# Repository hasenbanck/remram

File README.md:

# RemRam - 3D printer controller

## Features

 * 32bit STM32F765VI
   * 216 MHz
   * 512 KBytes RAM
   * 2 MBytes flash
 * 4x TMC2130 stepper driver
   * stealthChop
   * spreadCycle
   * coolStep
   * stallGuard
 * 24V main power rail
   * heatbed output (15A)
   * heater output (5A)
   * stepper driver and logic (5A)
 * 5V secondary power rail (3A)
   * FAN1 and FAN2
 * 2x 3.3V tertiary power rail (2x 0.5A)
   * MCU power (IO)
   * SD card power
 * Robust connectors
 * Quality, high powered MOSFET
 * 4 layer board with single side component placement

## PCB design

Software used KiCad 5.0

### Alternative Parts

You can substitute the TPS5408 with a TPS5402. In this case you also need to replace R4 with a Zero Ohm resistor.

## Compiling the firmware

 1. [Install Arduino](https://www.arduino.cc/en/Main/Software)
 2. [Install the STM32 Core](https://github.com/stm32duino/wiki/wiki/Getting-Started)
 3. Optional for Serial over USB support: [Update the STM32 Core using the git repository](https://github.com/stm32duino/wiki/wiki/Using-git-repository)
 4. [Download the current git branch of Marlin 2.0](https://github.com/MarlinFirmware/Marlin/tree/bugfix-2.0.x)
 5. Open the Marlin project, select the "RemRam V1" board from the Marlin menue, edit the Marlin configuration file and build the project. You need to find the HEX or BIN file that Arduino creates and flash the firmware onto the board (See: "How to flash the firmware").

## Configure Marlin

These are the board specific ```Configuration.h``` changes:
```C
#define SERIAL_PORT 1 // 1 = UART connection on EXT3
                      // -1 = Serial over USB (see: Virtual COM Port Support (Serial over USB))
                      // You can also configure SERIAL_PORT_2

#define BAUDRATE 115200 // 115200 for UART on EXT3
                        // 1000000 for Serial over USB

#define MOTHERBOARD BOARD_REMRAM_V1

#define X_DRIVER_TYPE  TMC2130
#define Y_DRIVER_TYPE  TMC2130
#define Z_DRIVER_TYPE  TMC2130
#define E0_DRIVER_TYPE TMC2130

#define ENDSTOP_INTERRUPTS_FEATURE

#define SDSUPPORT
```

These are the board specific ```Configuration_adv.h``` changes:
```C
#define MINIMUM_STEPPER_DIR_DELAY 20
#define MINIMUM_STEPPER_PULSE 0
#define MAXIMUM_STEPPER_RATE 400000

#if HAS_TRINAMIC

  // You can change ever value EXCEPT R_SENSE based on your setup.
  // Example values of my HEVO setup

  #define R_SENSE           0.12  // DO NOT CHANGE! Need to be 0.12 for RemRam V1
  #define HOLD_MULTIPLIER    0.3  // Scales down the holding current from run current
  #define INTERPOLATE       true  // Interpolate X/Y/Z_MICROSTEPS to 256

  #define X_CURRENT          750  // rms current in mA. Multiply by 1.41 for peak current.
  #define X_MICROSTEPS       256  // 0..256

  #define Y_CURRENT          750
  #define Y_MICROSTEPS       256

  #define Z_CURRENT          750
  #define Z_MICROSTEPS       256

  #define E0_CURRENT         400
  #define E0_MICROSTEPS      256

  #define STEALTHCHOP
  #define MONITOR_DRIVER_STATUS

  #if ENABLED(MONITOR_DRIVER_STATUS)
    #define CURRENT_STEP_DOWN     50  // [mA]
    #define REPORT_CURRENT_CHANGE
    #define STOP_ON_ERROR
  #endif

  #define SENSORLESS_HOMING // If you want to use sensorless homing

  #if ENABLED(SENSORLESS_HOMING) || ENABLED(SENSORLESS_PROBING)
    #define X_STALL_SENSITIVITY  2
    #define Y_STALL_SENSITIVITY  2
    #define Z_STALL_SENSITIVITY  2
  #endif

  #define TMC_DEBUG // Helpfull when setting up your system

#endif
```

```src/pins/pins_REMRAM_V1.h```
```C
// Use only one or the other (you could damage the hardware otherwise!)
#define SDSS               57   // Onboard SD card reader
//#define SDSS              9   // LCD SD card reader
```

Of course you need to aditionally change the configuration files based on your particular printer setup.

## Virtual COM Port Support (Serial over USB)

Virtual COM Port (also known as VCOM or CDC) support will land in the "official" STM32 arduino core with version 1.5.0. If you want to use VCOM feature earlier, you can use the the [master branch of the offical core](https://github.com/stm32duino/Arduino_Core_STM32).

Have a look at the "[Update the STM32 Core using the git repository](https://github.com/stm32duino/wiki/wiki/Using-git-repository)" on how to update the STM32 arduino core with a custom git branch. You also have to select "CDC Full Speed" as USB interface inside Arduino to enable the CDC interface.

## External SD card reader

Most RepRapDiscount based LCD modules come with an integrated SD card reader. You can use this reader, but because this system is 3.3V based, the signal to noise ration is higher. Meaning you will need a much better connection between the LCD module and the board. Crappy ribbon cables won't do it in most cases. Dropping the SPI speed AND using shielded ribbon cables is most likely needed to get a good signal integrity.

You can't use the onboard SD card reader and the LCD card reader at the same time. DO NOT insert a SD card in both slots at the same time, because this could lead to a hardware failure.

## How to flash the firmware

Supported:

 * Using the Cortex Debug Header (SWD)
 * Using DFU over USB
 * Using UART on EXT-3 PIN 15 (TX) and PIN 16 (RX)

### Cortex Debug Header

You can use the Cortex Debug Header to program the STM32 firmware and do step-by-step debugging.

This board only support SWD. SWO is not routed to the header, since we had to use the
pin for a PWM output.

I personally use the SEGGER J-Link Edu Mini. But any 2€ Ebay flasher should work ("ST Link V2").
Please make sure that you have a adapter for the debug header!

The debug header is a 2x05 pin (1.27/0.05”).

### DFU (USB)

https://www.st.com/en/development-tools/stsw-stm32080.html

Please pay attention that you don't just flash the HEX/BIN file, but the special DFU image file (*.dfu) you need to create with the "DFU file manager" tool. DfuSe will let you happily flash a HEX/BIN file, but the board won't boot without a propper DFU file.

Please read the "UM0412" user manual you can find at the above link.

### UART

https://www.st.com/en/development-tools/flasher-stm32.html

## LICENSE

CERN OHL version 1.2

The files under PCB/packages3d are excluded from this license and are provided under fair use terms for this open-source project.

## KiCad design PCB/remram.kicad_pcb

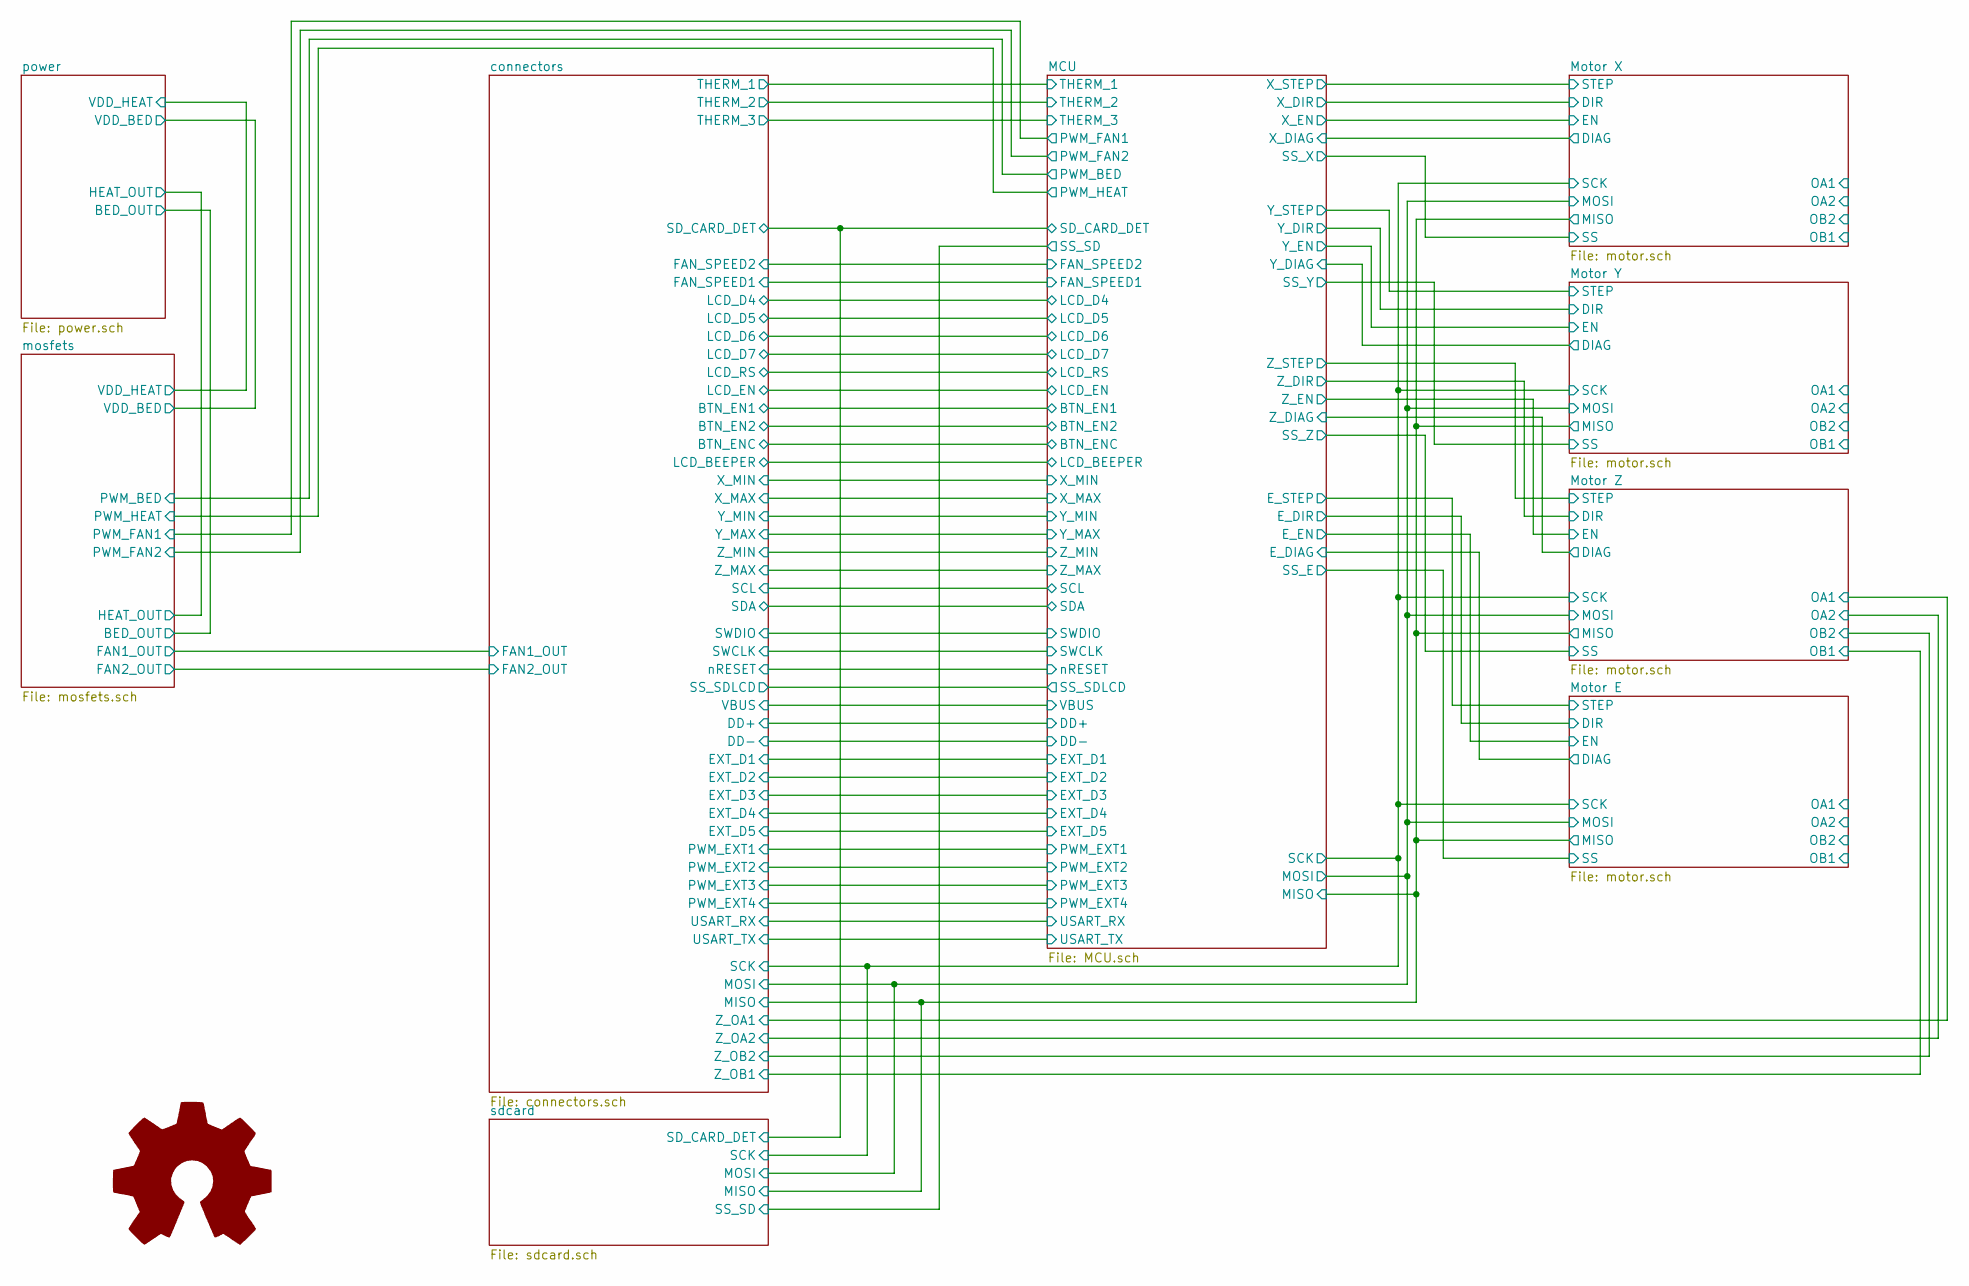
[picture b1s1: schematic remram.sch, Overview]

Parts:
LOGO1: Logo_Open_Hardware_Large; OSHW-Logo2_14.6x12mm_SilkScreen

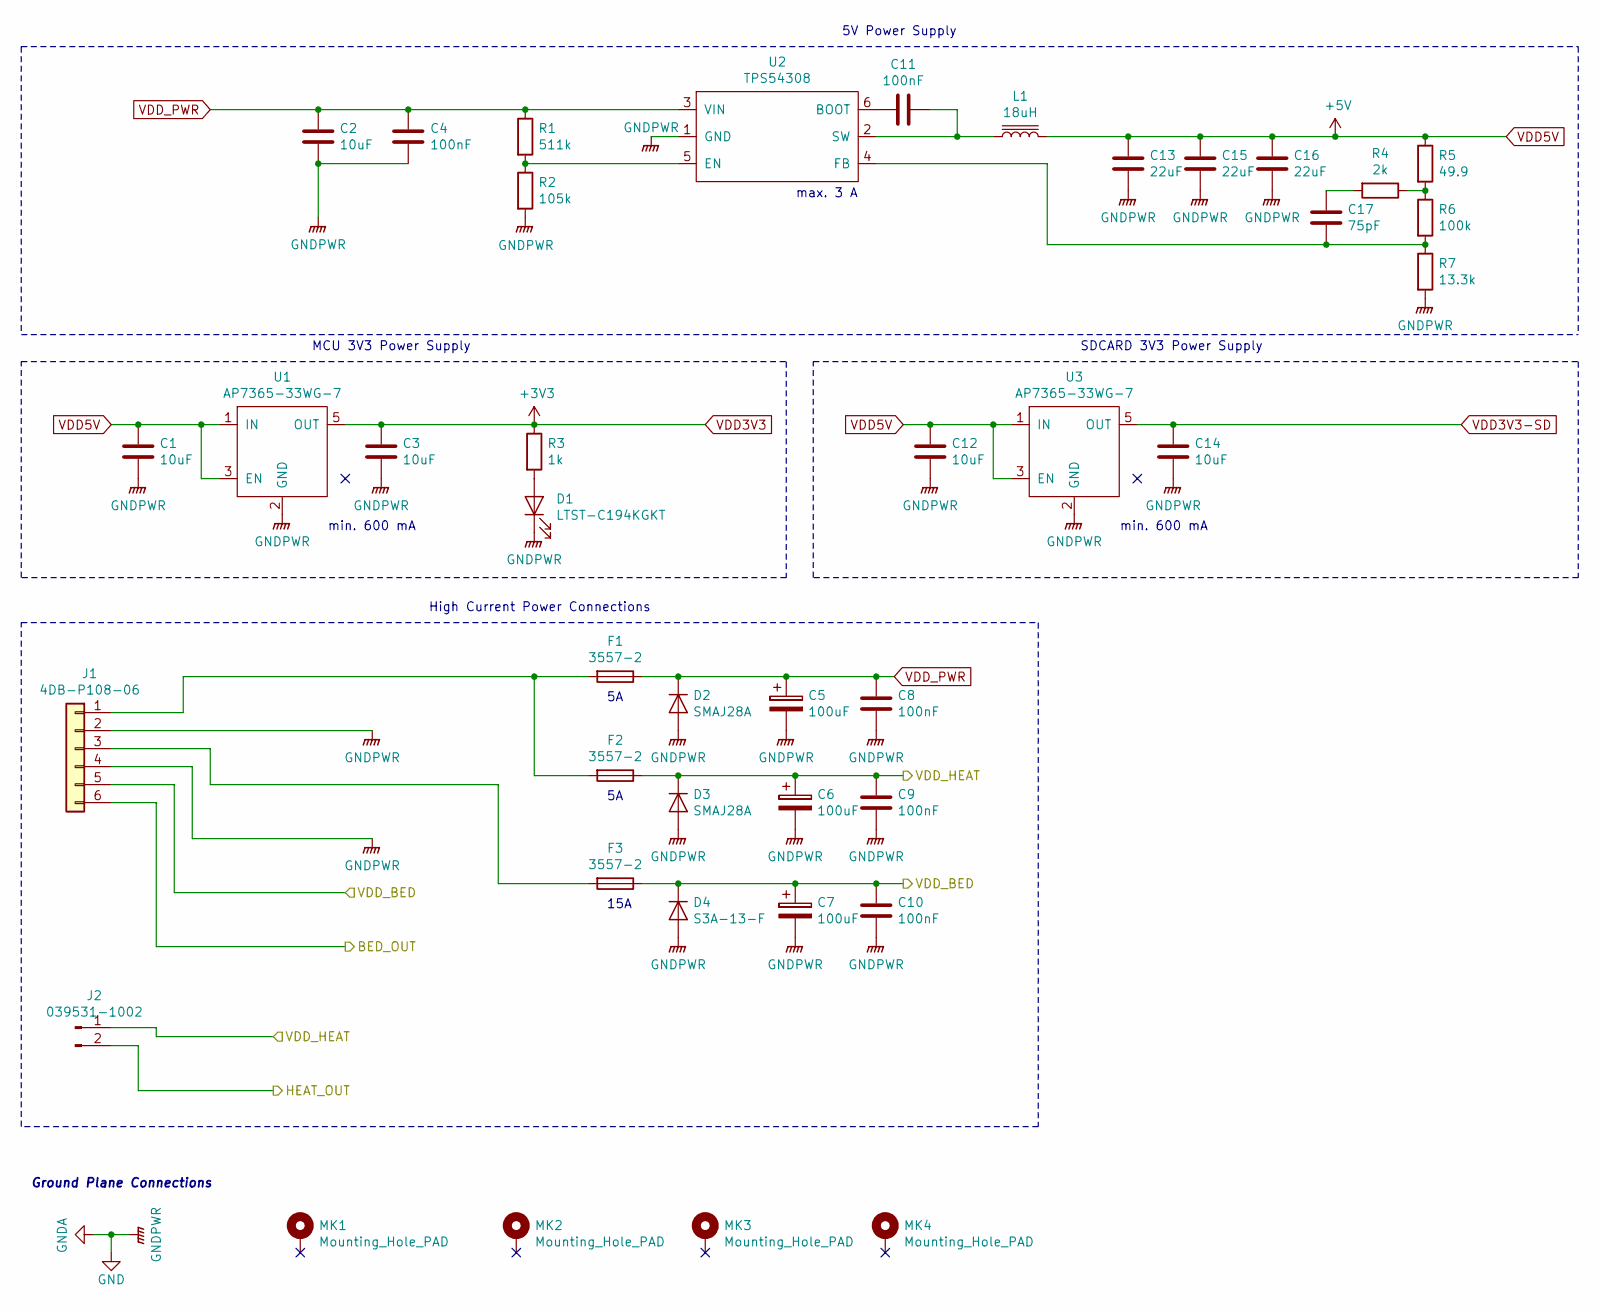
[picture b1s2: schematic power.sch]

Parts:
C1, C3, C12, C14: 10uF; C_0603_1608Metric
C2: 10uF; C_1206_3216Metric
C4: 100nF; C_1206_3216Metric
C5, C6, C7: 100uF; CP_Radial_D6.3mm_P2.50mm
C8, C9, C10: 100nF; C_1812_4532Metric
C11: 100nF; C_0603_1608Metric
C13, C15, C16: 22uF; C_1206_3216Metric
C17: 75pF; C_0603_1608Metric
D1: LTST-C194KGKT; LED_0603_1608Metric
D2, D3: SMAJ28A; D_SMA
D4: S3A-13-F; D_SMC
F1, F2, F3: 3557-2; KEYSTONE-FUSE-3557-2
J1: 4DB-P108-06
J2: 039531-1002; 39531-1002
L1: 18uH; L_Wuerth_WE-PDF
MK1, MK2, MK3, MK4: Mounting_Hole_PAD; MountingHole_3.5mm_Pad
R1: 511k; R_0603_1608Metric
R2: 105k; R_0603_1608Metric
R3: 1k; R_0603_1608Metric
R4: 2k; R_0603_1608Metric
R5: 49.9; R_0603_1608Metric
R6: 100k; R_0603_1608Metric
R7: 13.3k; R_0603_1608Metric
U1, U3: AP7365-33WG-7; SOT-23-5
U2: TPS54308; SOT-23-6

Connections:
/mosfets/BED_OUT: J1.6; also elsewhere on the board
/mosfets/HEAT_OUT: J2.2; also elsewhere on the board
/mosfets/VDD_BED: C7.1, C10.1, D4.1 (K), F3.1, J1.5; also elsewhere on the board
/mosfets/VDD_HEAT: C6.1, C9.1, D3.1 (K), F2.1, J2.1; also elsewhere on the board
GND: C1.2, C2.2, C3.2, C4.2, C5.2, C6.2, C7.2, C8.2, C9.2, C10.2, C12.2, C13.2, C14.2, C15.2, C16.2, D1.1 (K), D2.2 (A), D3.2 (A), D4.2 (A), J1.2, J1.4, R2.2, R7.2, U1.2 (GND), U2.1 (GND), U3.2 (GND); also elsewhere on the board
unnamed: C11.1, U2.6 (BOOT)
unnamed: C11.2, L1.1, U2.2 (SW)
unnamed: C17.1, R4.2
unnamed: C17.2, R6.2, R7.1, U2.4 (FB)
unnamed: D1.2 (A), R3.2
unnamed: F1.2, F2.2, J1.1
unnamed: F3.2, J1.3
unnamed: R1.2, R2.1, U2.5 (EN)
unnamed: R4.1, R5.2, R6.1
VDD3V3: C3.1, R3.1, U1.5 (OUT); also elsewhere on the board
VDD3V3-SD: C14.1, U3.5 (OUT); also elsewhere on the board
VDD5V: C1.1, C12.1, C13.1, C15.1, C16.1, L1.2, R5.1, U1.1 (IN), U1.3 (EN), U3.1 (IN), U3.3 (EN); also elsewhere on the board
VDD_PWR: C2.1, C4.1, C5.1, C8.1, D2.1 (K), F1.1, R1.1, U2.3 (VIN); also elsewhere on the board

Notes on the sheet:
min. 600 mA
max. 3 A
15A
Ground Plane Connections
High Current Power Connections
5V Power Supply
MCU 3V3 Power Supply
SDCARD 3V3 Power Supply

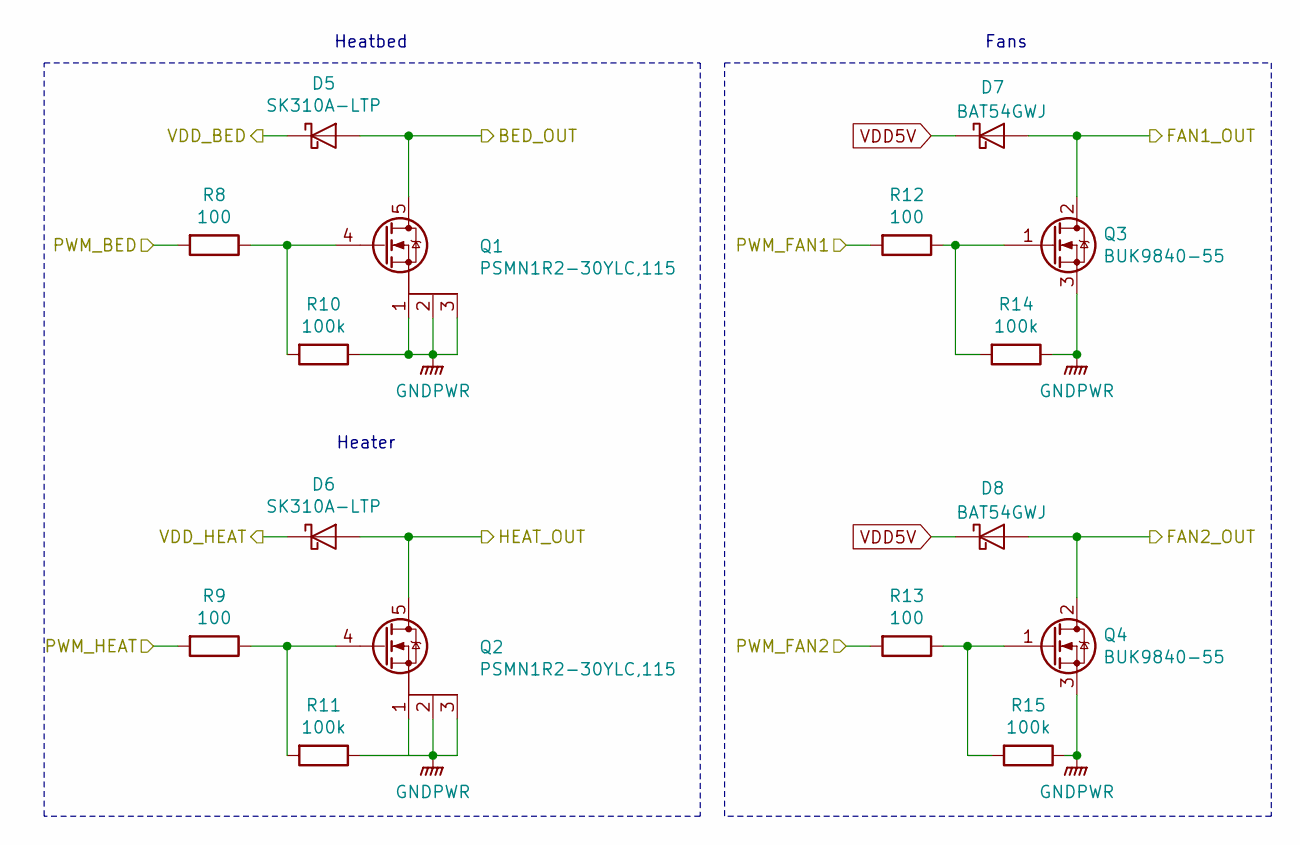
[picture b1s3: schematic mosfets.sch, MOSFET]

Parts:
D5, D6: SK310A-LTP; D_SMA
D7, D8: BAT54GWJ; D_SOD-123
Q1, Q2: PSMN1R2-30YLC,115; SOT-669_LFPAK_ThermalVias-1
Q3, Q4: BUK9840-55; SOT-223-3_TabPin2
R8, R9, R12, R13: 100; R_0603_1608Metric
R10, R11, R14, R15: 100k; R_0603_1608Metric

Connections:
/MCU/PWM_BED: R8.2; also elsewhere on the board
/MCU/PWM_FAN1: R12.2; also elsewhere on the board
/MCU/PWM_FAN2: R13.2; also elsewhere on the board
/MCU/PWM_HEAT: R9.2; also elsewhere on the board
/connectors/FAN1_OUT: D7.2 (A), Q3.2 (D); also elsewhere on the board
/connectors/FAN2_OUT: D8.2 (A), Q4.2 (D); also elsewhere on the board
/mosfets/BED_OUT: D5.2 (A), Q1.5 (D); also elsewhere on the board
/mosfets/HEAT_OUT: D6.2 (A), Q2.5 (D); also elsewhere on the board
/mosfets/VDD_BED: D5.1 (K); also elsewhere on the board
/mosfets/VDD_HEAT: D6.1 (K); also elsewhere on the board
GND: Q1.1 (S), Q1.2 (S), Q1.3 (S), Q2.1 (S), Q2.2 (S), Q2.3 (S), Q3.3 (S), Q4.3 (S), R10.1, R11.1, R14.1, R15.1; also elsewhere on the board
unnamed: Q1.4 (G), R8.1, R10.2
unnamed: Q2.4 (G), R9.1, R11.2
unnamed: Q3.1 (G), R12.1, R14.2
unnamed: Q4.1 (G), R13.1, R15.2
VDD5V: D7.1 (K), D8.1 (K); also elsewhere on the board

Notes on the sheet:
Heater
Heatbed
Fans

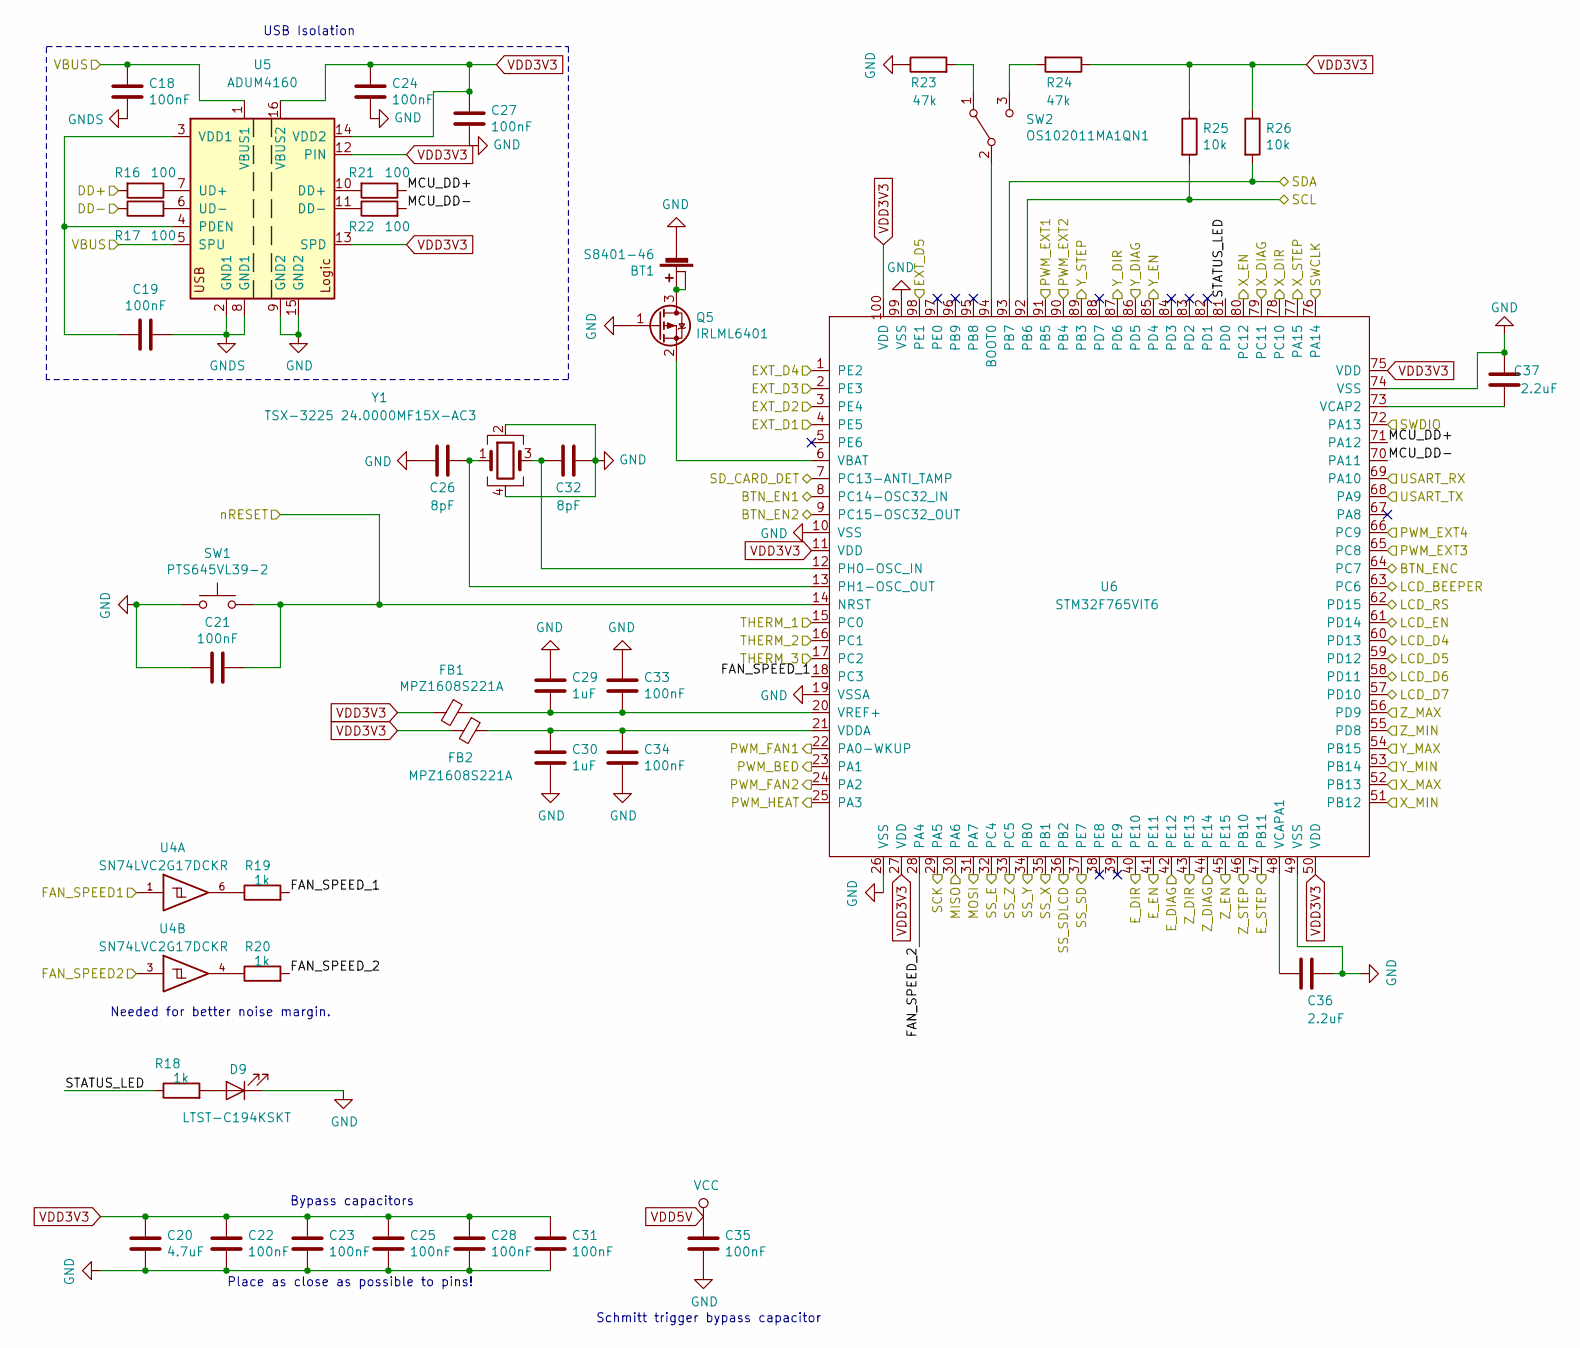
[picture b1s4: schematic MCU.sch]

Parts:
BT1: S8401-46
C18, C19, C21, C22, C23, C24, C25, C27, C28, C31, C33, C34, C35: 100nF; C_0603_1608Metric
C20: 4.7uF; C_0603_1608Metric
C26, C32: 8pF; C_0603_1608Metric
C29, C30: 1uF; C_0603_1608Metric
C36, C37: 2.2uF; C_0603_1608Metric
D9: LTST-C194KSKT; LED_0603_1608Metric
FB1, FB2: MPZ1608S221A; R_0603_1608Metric
Q5: IRLML6401; SOT-23
R16, R17, R21, R22: 100; R_0603_1608Metric
R18, R19, R20: 1k; R_0603_1608Metric
R23, R24: 47k; R_0603_1608Metric
R25, R26: 10k; R_0603_1608Metric
SW1: PTS645VL39-2; SW_Tactile_SPST_Angled_PTS645Vx39-2LFS
SW2: OS102011MA1QN1; SW_CuK_OS102011MA1QN1_SPDT_Angled
U4: SN74LVC2G17DCKR; SOT-363_SC-70-6
U5: ADUM4160; SOIC-16W_7.5x10.3mm_P1.27mm
U6: STM32F765VIT6; TQFP-100_14x14mm_P0.5mm
Y1: TSX-3225 24.0000MF15X-AC3; Crystal_SMD_SeikoEpson_TSX3225-4Pin_3.2x2.5mm

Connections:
/MCU/BTN_EN1: U6.8 (PC14-OSC32_IN); also elsewhere on the board
/MCU/BTN_EN2: U6.9 (PC15-OSC32_OUT); also elsewhere on the board
/MCU/BTN_ENC: U6.64 (PC7); also elsewhere on the board
/MCU/DD+: R16.2; also elsewhere on the board
/MCU/DD-: R17.1; also elsewhere on the board
/MCU/EXT_D1: U6.4 (PE5); also elsewhere on the board
/MCU/EXT_D2: U6.3 (PE4); also elsewhere on the board
/MCU/EXT_D3: U6.2 (PE3); also elsewhere on the board
/MCU/EXT_D4: U6.1 (PE2); also elsewhere on the board
/MCU/EXT_D5: U6.98 (PE1); also elsewhere on the board
/MCU/E_STEP: U6.47 (PB11); also elsewhere on the board
/MCU/FAN_SPEED1: U4.1; also elsewhere on the board
/MCU/FAN_SPEED2: U4.3; also elsewhere on the board
/MCU/FAN_SPEED_1: R19.2, U6.18 (PC3)
/MCU/FAN_SPEED_2: R20.2, U6.28 (PA4)
/MCU/LCD_BEEPER: U6.63 (PC6); also elsewhere on the board
/MCU/LCD_D4: U6.60 (PD13); also elsewhere on the board
/MCU/LCD_D5: U6.59 (PD12); also elsewhere on the board
/MCU/LCD_D6: U6.58 (PD11); also elsewhere on the board
/MCU/LCD_D7: U6.57 (PD10); also elsewhere on the board
/MCU/LCD_EN: U6.61 (PD14); also elsewhere on the board
/MCU/LCD_RS: U6.62 (PD15); also elsewhere on the board
/MCU/MCU_DD+: R21.1, U6.71 (PA12)
/MCU/MCU_DD-: R22.2, U6.70 (PA11)
/MCU/MISO: U6.30 (PA6); also elsewhere on the board
/MCU/MOSI: U6.31 (PA7); also elsewhere on the board
/MCU/PWM_BED: U6.23 (PA1); also elsewhere on the board
/MCU/PWM_EXT1: U6.91 (PB5); also elsewhere on the board
/MCU/PWM_EXT2: U6.90 (PB4); also elsewhere on the board
/MCU/PWM_EXT3: U6.65 (PC8); also elsewhere on the board
/MCU/PWM_EXT4: U6.66 (PC9); also elsewhere on the board
/MCU/PWM_FAN1: U6.22 (PA0-WKUP); also elsewhere on the board
/MCU/PWM_FAN2: U6.24 (PA2); also elsewhere on the board
/MCU/PWM_HEAT: U6.25 (PA3); also elsewhere on the board
/MCU/SCK: U6.29 (PA5); also elsewhere on the board
/MCU/SCL: R25.2, U6.92 (PB6); also elsewhere on the board
/MCU/SDA: R26.2, U6.93 (PB7); also elsewhere on the board
/MCU/SD_CARD_DET: U6.7 (PC13-ANTI_TAMP); also elsewhere on the board
/MCU/SS_SD: U6.37 (PE7); also elsewhere on the board
/MCU/SS_SDLCD: U6.36 (PB2); also elsewhere on the board
/MCU/STATUS_LED: R18.1, U6.81 (PD0)
/MCU/SWCLK: U6.76 (PA14); also elsewhere on the board
/MCU/SWDIO: U6.72 (PA13); also elsewhere on the board
/MCU/THERM_1: U6.15 (PC0); also elsewhere on the board
/MCU/THERM_2: U6.16 (PC1); also elsewhere on the board
/MCU/THERM_3: U6.17 (PC2); also elsewhere on the board
/MCU/USART_RX: U6.69 (PA10); also elsewhere on the board
/MCU/USART_TX: U6.68 (PA9); also elsewhere on the board
/MCU/VBUS: C18.1, U5.1 (VBUS1), U5.5 (SPU); also elsewhere on the board
/MCU/X_MAX: U6.52 (PB13); also elsewhere on the board
/MCU/X_MIN: U6.51 (PB12); also elsewhere on the board
/MCU/Y_MAX: U6.54 (PB15); also elsewhere on the board
/MCU/Y_MIN: U6.53 (PB14); also elsewhere on the board
/MCU/Z_MAX: U6.56 (PD9); also elsewhere on the board
/MCU/Z_MIN: U6.55 (PD8); also elsewhere on the board
/MCU/nRESET: C21.2, SW1.2, U6.14 (NRST); also elsewhere on the board
/Motor E/DIAG: U6.42 (PE12); also elsewhere on the board
/Motor E/DIR: U6.40 (PE10); also elsewhere on the board
/Motor E/EN: U6.41 (PE11); also elsewhere on the board
/Motor E/SS: U6.32 (PC4); also elsewhere on the board
/Motor X/DIAG: U6.79 (PC11); also elsewhere on the board
/Motor X/DIR: U6.78 (PC10); also elsewhere on the board
/Motor X/EN: U6.80 (PC12); also elsewhere on the board
/Motor X/SS: U6.35 (PB1); also elsewhere on the board
/Motor X/STEP: U6.77 (PA15); also elsewhere on the board
/Motor Y/DIAG: U6.86 (PD5); also elsewhere on the board
/Motor Y/DIR: U6.87 (PD6); also elsewhere on the board
/Motor Y/EN: U6.85 (PD4); also elsewhere on the board
/Motor Y/SS: U6.34 (PB0); also elsewhere on the board
/Motor Y/STEP: U6.89 (PB3); also elsewhere on the board
/Motor Z/DIAG: U6.44 (PE14); also elsewhere on the board
/Motor Z/DIR: U6.43 (PE13); also elsewhere on the board
/Motor Z/EN: U6.45 (PE15); also elsewhere on the board
/Motor Z/SS: U6.33 (PC5); also elsewhere on the board
/Motor Z/STEP: U6.46 (PB10); also elsewhere on the board
GND: BT1.1 (-), C20.2, C21.1, C22.2, C23.2, C24.2, C25.2, C26.1, C27.1, C28.2, C29.1, C30.2, C31.2, C32.2, C33.1, C34.2, C35.2, C36.1, C37.2, D9.1 (K), Q5.1 (G), R23.1, SW1.1, U4.2 (GND), U5.9 (GND2), U5.15 (GND2), U6.10 (VSS), U6.19 (VSSA), U6.26 (VSS), U6.49 (VSS), U6.74 (VSS), U6.99 (VSS), Y1.2, Y1.4; also elsewhere on the board
GNDS: C18.2, C19.1, U5.2 (GND1), U5.8 (GND1); also elsewhere on the board
unnamed: BT1.2 (+), BT1.3 (+), Q5.3 (D)
unnamed: C19.2, U5.3 (VDD1), U5.4 (PDEN)
unnamed: C26.2, U6.13 (PH1-OSC_OUT), Y1.1
unnamed: C29.2, C33.2, FB1.1, U6.20 (VREF+)
unnamed: C30.1, C34.1, FB2.1, U6.21 (VDDA)
unnamed: C32.1, U6.12 (PH0-OSC_IN), Y1.3
unnamed: C36.2, U6.48 (VCAPA1)
unnamed: C37.1, U6.73 (VCAP2)
unnamed: D9.2 (A), R18.2
unnamed: Q5.2 (S), U6.6 (VBAT)
unnamed: R16.1, U5.7 (UD+)
unnamed: R17.2, U5.6 (UD-)
unnamed: R19.1, U4.6
unnamed: R20.1, U4.4
unnamed: R21.2, U5.10 (DD+)
unnamed: R22.1, U5.11 (DD-)
unnamed: R23.2, SW2.1 (A)
unnamed: R24.2, SW2.3 (C)
unnamed: SW2.2 (B), U6.94 (BOOT0)
VDD3V3: C20.1, C22.1, C23.1, C24.1, C25.1, C27.2, C28.1, C31.1, FB1.2, FB2.2, R24.1, R25.1, R26.1, U5.12 (PIN), U5.13 (SPD), U5.14 (VDD2), U5.16 (VBUS2), U6.11 (VDD), U6.27 (VDD), U6.50 (VDD), U6.75 (VDD), U6.100 (VDD); also elsewhere on the board
VDD5V: C35.1, U4.5 (VCC); also elsewhere on the board

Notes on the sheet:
Place as close as possible to pins!
Bypass capacitors
USB Isolation
Needed for better noise margin.
Schmitt trigger bypass capacitor

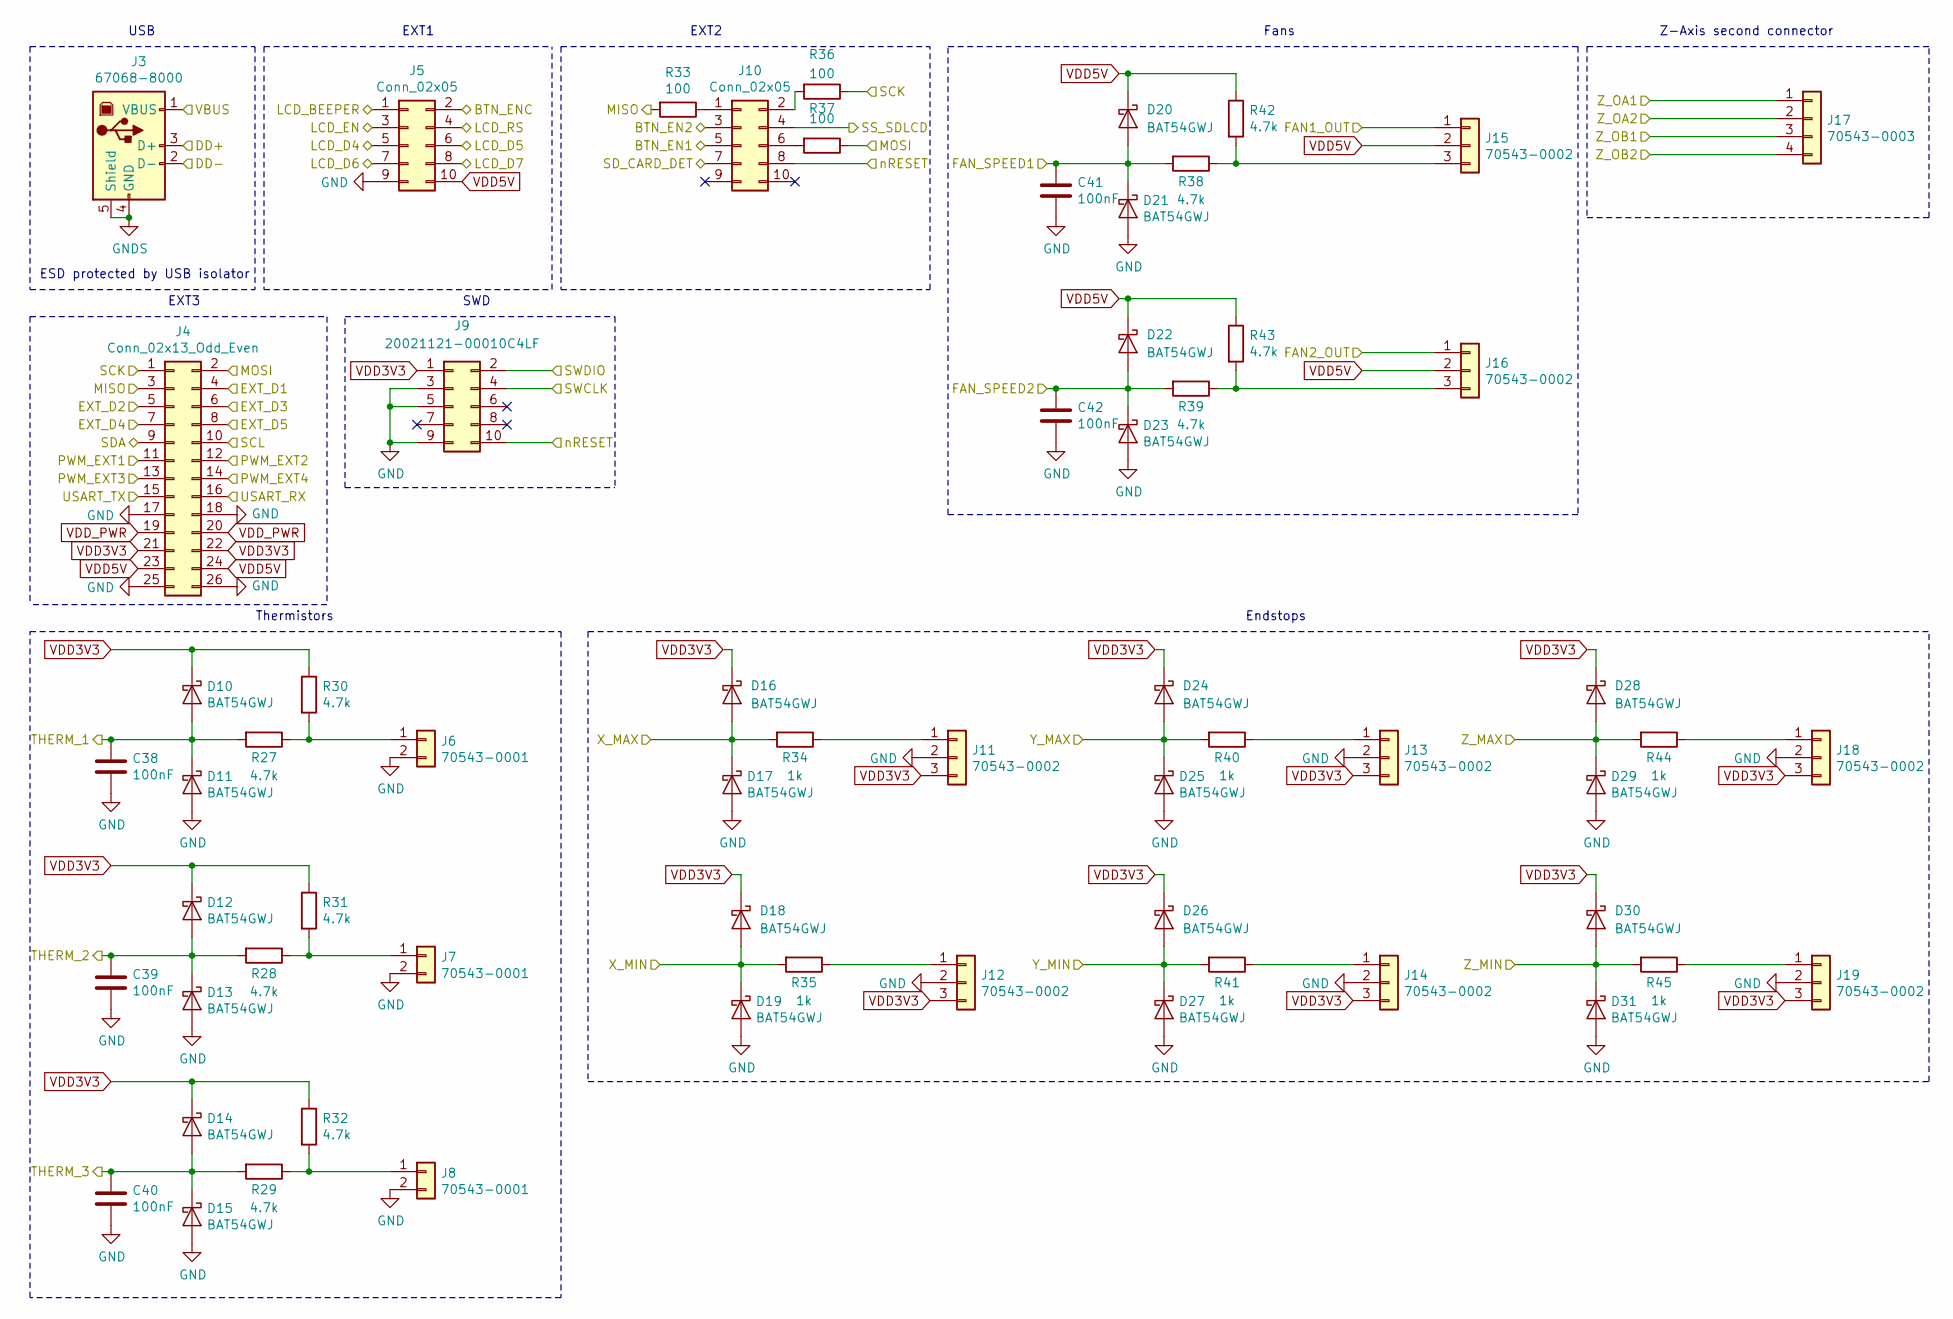
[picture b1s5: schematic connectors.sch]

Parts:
C38, C39, C40, C41, C42: 100nF; C_0603_1608Metric
D10, D11, D12, D13, D14, D15, D16, D17, D18, D19, D20, D21, D22, D23, D24, D25, D26, D27, D28, D29, D30, D31: BAT54GWJ; D_SOD-123
J3: 67068-8000
J4: Conn_02x13_Odd_Even; PinHeader_2x13_P2.54mm_Vertical
J5, J10: Conn_02x05; PinHeader_2x05_P2.54mm_Vertical
J6, J7, J8: 70543-0001
J9: 20021121-00010C4LF; PinHeader_2x05_P1.27mm_Vertical_SMD
J11, J12, J13, J14, J15, J16, J18, J19: 70543-0002
J17: 70543-0003
R27, R28, R29, R30, R31, R32, R38, R39, R42, R43: 4.7k; R_0603_1608Metric
R33, R36, R37: 100; R_0603_1608Metric
R34, R35, R40, R41, R44, R45: 1k; R_0603_1608Metric

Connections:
/MCU/BTN_EN1: J10.5; also elsewhere on the board
/MCU/BTN_EN2: J10.3; also elsewhere on the board
/MCU/BTN_ENC: J5.2; also elsewhere on the board
/MCU/DD+: J3.3 (D+); also elsewhere on the board
/MCU/DD-: J3.2 (D-); also elsewhere on the board
/MCU/EXT_D1: J4.4; also elsewhere on the board
/MCU/EXT_D2: J4.5; also elsewhere on the board
/MCU/EXT_D3: J4.6; also elsewhere on the board
/MCU/EXT_D4: J4.7; also elsewhere on the board
/MCU/EXT_D5: J4.8; also elsewhere on the board
/MCU/FAN_SPEED1: C41.1, D20.2 (A), D21.1 (K), R38.2; also elsewhere on the board
/MCU/FAN_SPEED2: C42.1, D22.2 (A), D23.1 (K), R39.2; also elsewhere on the board
/MCU/LCD_BEEPER: J5.1; also elsewhere on the board
/MCU/LCD_D4: J5.5; also elsewhere on the board
/MCU/LCD_D5: J5.6; also elsewhere on the board
/MCU/LCD_D6: J5.7; also elsewhere on the board
/MCU/LCD_D7: J5.8; also elsewhere on the board
/MCU/LCD_EN: J5.3; also elsewhere on the board
/MCU/LCD_RS: J5.4; also elsewhere on the board
/MCU/MISO: J4.3, R33.2; also elsewhere on the board
/MCU/MOSI: J4.2, R37.1; also elsewhere on the board
/MCU/PWM_EXT1: J4.11; also elsewhere on the board
/MCU/PWM_EXT2: J4.12; also elsewhere on the board
/MCU/PWM_EXT3: J4.13; also elsewhere on the board
/MCU/PWM_EXT4: J4.14; also elsewhere on the board
/MCU/SCK: J4.1, R36.1; also elsewhere on the board
/MCU/SCL: J4.10; also elsewhere on the board
/MCU/SDA: J4.9; also elsewhere on the board
/MCU/SD_CARD_DET: J10.7; also elsewhere on the board
/MCU/SS_SDLCD: J10.4; also elsewhere on the board
/MCU/SWCLK: J9.4; also elsewhere on the board
/MCU/SWDIO: J9.2; also elsewhere on the board
/MCU/THERM_1: C38.1, D10.2 (A), D11.1 (K), R27.2; also elsewhere on the board
/MCU/THERM_2: C39.1, D12.2 (A), D13.1 (K), R28.2; also elsewhere on the board
/MCU/THERM_3: C40.1, D14.2 (A), D15.1 (K), R29.2; also elsewhere on the board
/MCU/USART_RX: J4.16; also elsewhere on the board
/MCU/USART_TX: J4.15; also elsewhere on the board
/MCU/VBUS: J3.1 (VBUS); also elsewhere on the board
/MCU/X_MAX: D16.2 (A), D17.1 (K), R34.2; also elsewhere on the board
/MCU/X_MIN: D18.2 (A), D19.1 (K), R35.2; also elsewhere on the board
/MCU/Y_MAX: D24.2 (A), D25.1 (K), R40.2; also elsewhere on the board
/MCU/Y_MIN: D26.2 (A), D27.1 (K), R41.2; also elsewhere on the board
/MCU/Z_MAX: D28.2 (A), D29.1 (K), R44.2; also elsewhere on the board
/MCU/Z_MIN: D30.2 (A), D31.1 (K), R45.2; also elsewhere on the board
/MCU/nRESET: J9.10, J10.8; also elsewhere on the board
/Motor Z/OA1: J17.1; also elsewhere on the board
/Motor Z/OA2: J17.2; also elsewhere on the board
/Motor Z/OB1: J17.3; also elsewhere on the board
/Motor Z/OB2: J17.4; also elsewhere on the board
/connectors/FAN1_OUT: J15.1; also elsewhere on the board
/connectors/FAN2_OUT: J16.1; also elsewhere on the board
GND: C38.2, C39.2, C40.2, C41.2, C42.2, D11.2 (A), D13.2 (A), D15.2 (A), D17.2 (A), D19.2 (A), D21.2 (A), D23.2 (A), D25.2 (A), D27.2 (A), D29.2 (A), D31.2 (A), J4.17, J4.18, J4.25, J4.26, J5.9, J6.2, J7.2, J8.2, J9.3, J9.5, J9.9, J11.2, J12.2, J13.2, J14.2, J18.2, J19.2; also elsewhere on the board
GNDS: J3.4 (GND), J3.5 (Shield); also elsewhere on the board
unnamed: J6.1, R27.1, R30.2
unnamed: J7.1, R28.1, R31.2
unnamed: J8.1, R29.1, R32.2
unnamed: J10.1, R33.1
unnamed: J10.2, R36.2
unnamed: J10.6, R37.2
unnamed: J11.1, R34.1
unnamed: J12.1, R35.1
unnamed: J13.1, R40.1
unnamed: J14.1, R41.1
unnamed: J15.3, R38.1, R42.2
unnamed: J16.3, R39.1, R43.2
unnamed: J18.1, R44.1
unnamed: J19.1, R45.1
VDD3V3: D10.1 (K), D12.1 (K), D14.1 (K), D16.1 (K), D18.1 (K), D24.1 (K), D26.1 (K), D28.1 (K), D30.1 (K), J4.21, J4.22, J9.1, J11.3, J12.3, J13.3, J14.3, J18.3, J19.3, R30.1, R31.1, R32.1; also elsewhere on the board
VDD5V: D20.1 (K), D22.1 (K), J4.23, J4.24, J5.10, J15.2, J16.2, R42.1, R43.1; also elsewhere on the board
VDD_PWR: J4.19, J4.20; also elsewhere on the board

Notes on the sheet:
USB
EXT1
EXT2
EXT3
Thermistors
Endstops
SWD
ESD protected by USB isolator
Fans
Z-Axis second connector
